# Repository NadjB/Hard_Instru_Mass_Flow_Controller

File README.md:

View this project on [CADLAB.io](https://cadlab.io/project/27497). 

# Hard_Instru_Mass_Flow_Controller

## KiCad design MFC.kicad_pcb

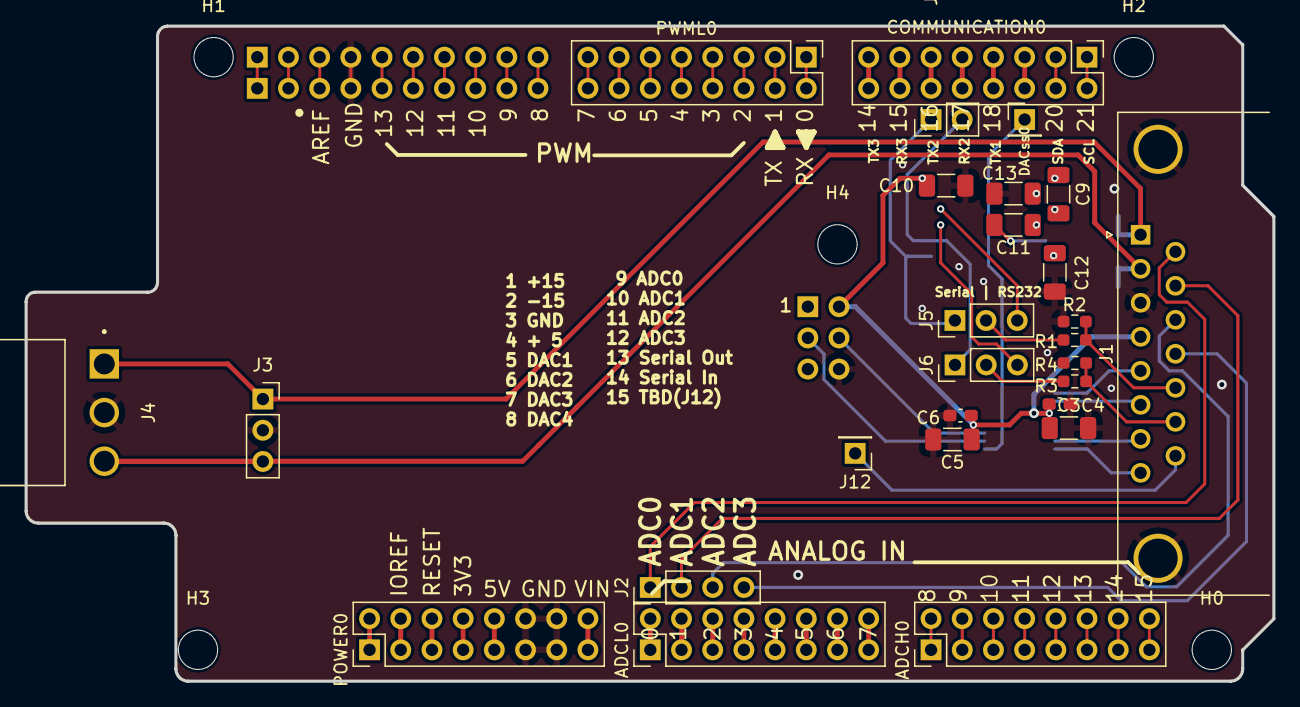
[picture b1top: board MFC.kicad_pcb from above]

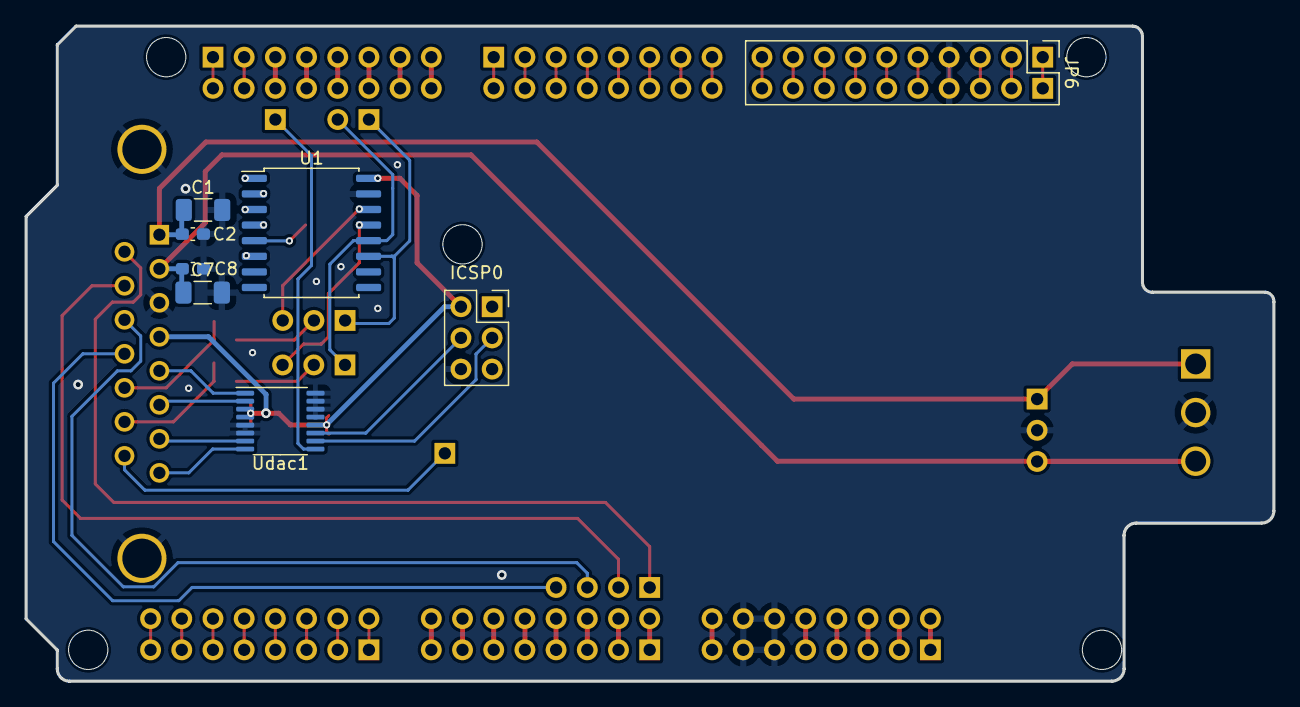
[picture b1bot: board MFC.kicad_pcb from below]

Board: 2 copper layers, 101.6 x 53.3 mm, 40 parts (8 on the bottom side), 32 nets.

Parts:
ADCH0: FH254-108DF08500V; PinHeader_1x08_P2.54mm_Vertical_Double
ADCL0: FH254-108DF08500V; PinHeader_1x08_P2.54mm_Vertical_Double
C1, C3, C5, C7: 10µF; C_1206_3216Metric_Pad1.33x1.80mm_HandSolder
C2, C4, C6, C8: 100nF; C_0603_1608Metric_Pad1.08x0.95mm_HandSolder
C9, C10, C11, C12, C13: 1µF; C_1206_3216Metric_Pad1.33x1.80mm_HandSolder
COMMUNICATION0: FH254-108DF08500V; PinHeader_1x08_P2.54mm_Vertical_Double
DACss0: Conn_01x01_Pin; PinHeader_1x01_P2.54mm_Vertical
H0, H1, H2, H3, H4: MountingHole_Pad; MountingHole_3.2mm_M3
ICSP0: ICSP; PinSocket_2x03_P2.54mm_Vertical
J1: DA15_Receptacle_MountingHoles; DSUB-15_Female_Horizontal_P2.77x2.84mm_EdgePinOffset7.70mm_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
J2: Conn_01x04_Pin; PinHeader_1x04_P2.54mm_Vertical
J3: Conn_01x03_Socket; PinSocket_1x03_P2.54mm_Vertical
J4: 647676-3
J5, J6: Conn_01x03_Pin; PinHeader_1x03_P2.54mm_Vertical
J7: Conn_01x02_Pin; PinHeader_1x02_P2.54mm_Vertical
J12: Conn_01x01_Pin; PinHeader_1x01_P2.54mm_Vertical
JP6: FH254-110DF08500V; PinHeader_1x10_P2.54mm_Vertical_Double
POWER0: FH254-108DF08500V; PinHeader_1x08_P2.54mm_Vertical_Double
PWML0: FH254-108DF08500V; PinHeader_1x08_P2.54mm_Vertical_Double
R1, R3: 0; R_0603_1608Metric_Pad0.98x0.95mm_HandSolder
R2, R4: R; R_0603_1608Metric_Pad0.98x0.95mm_HandSolder
U1: MAX232; SOIC-16W_7.5x10.3mm_P1.27mm
Udac1: DAC8554IPW; TSSOP-16_4.4x5mm_P0.65mm

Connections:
+5V: C3.1, C4.1, C5.1, C6.1, C10.1, ICSP0.2, J1.4, U1.16 (VCC), Udac1.3 (V_{REF}H), Udac1.4 (AV_{DD}), Udac1.12 (IOV_{DD})
+15V: C1.1, C2.1, J1.1, J3.1, J4.1
-15V: C7.1, C8.1, J1.2, J3.3, J4.3
/CAD0: J1.9, J2.1
/CAD1: J1.10, J2.2
/CAD2: J1.11 (P111), J2.3
/CAD3: J1.12, J2.4
/DAC_{1}: J1.5, Udac1.1 (V_{OUT}A)
/DAC_{2}: J1.6, Udac1.2 (V_{OUT}B)
/DAC_{3}: J1.7, Udac1.7 (V_{OUT}C)
/DAC_{4}: J1.8, Udac1.8 (V_{OUT}D)
/MOSI: ICSP0.4, Udac1.11 (DIN)
/PB1: ICSP0.3, Udac1.10 (SCLK)
/RS232_MISO: J6.3, U1.13 (R1IN)
/RS232_MOSI: J5.3, U1.14 (T1OUT)
/RX2: J6.1, J7.2, U1.12 (R1OUT)
/SCL: COMMUNICATION0.1, JP6.1
/SDA: COMMUNICATION0.2, JP6.2
/SS: DACss0.1, Udac1.9 (~SYNC)
/Serial_MISO: J1.14, R3.2, R4.1
/Serial_MOSI: J1.13, R1.2, R2.1
/TX2: J5.1, J7.1, U1.11 (T1IN)
GND: C1.2, C2.2, C3.2, C4.2, C5.2, C6.2, C7.2, C8.2, C10.2, C12.2, C13.2, ICSP0.6, J1.0 (PAD), J1.3, J3.2, J4.2, JP6.4, POWER0.6, POWER0.7, R2.2, R4.2, U1.15 (GND), Udac1.5 (V_{REF}L), Udac1.6 (GND), Udac1.13 (A0), Udac1.14 (A1), Udac1.15 (~ENABLE), Udac1.16 (LDAC)
unnamed: J1.15, J12.1
unnamed: J5.2, R1.1
unnamed: J6.2, R3.1
unnamed: C9.1, U1.1 (C1+)
unnamed: C9.2, U1.3 (C1-)
unnamed: C11.1, U1.4 (C2+)
unnamed: C11.2, U1.5 (C2-)
unnamed: C13.1, U1.2 (VS+)
unnamed: C12.1, U1.6 (VS-)

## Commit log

2022-11-28 From first fab: - Error corrected: - Schema : Connect DAC to MOSI (instead of MISO) - PCB : silkscreen ADC 0 to 3 (instead of DAC0-3) - Optimisation in PCB : - use the doubleRow library and doubled e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
2023-03-20 Update to KiCad 7
2023-03-20 Reduced space between +15 and -15 transversal header to fit 5.08 connectors
2023-07-21 Cleaned up DoubleRow
2023-07-24 Changed transversal power connector
2023-07-25 Added MAX232 Optimised DAC8554 Routing
2023-07-25 First routing done
2023-07-28 Added choice for serial com
2023-08-21 Update 10u capa for tantal
2023-09-20 Minor change for better ground coverage
2023-11-03 Backlink to CADLAB.io has been added.
2023-12-01 Fabricated 10/10/23
2025-03-28 Updated to kicad 9
